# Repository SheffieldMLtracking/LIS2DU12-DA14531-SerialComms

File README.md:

# LIS2DU12-DA14531-SerialComms
Repo to develop LIS2DU12 communications with DA14531 BLE enabled microcontroller.

I've used the blinky example here to build the i2c stuff!

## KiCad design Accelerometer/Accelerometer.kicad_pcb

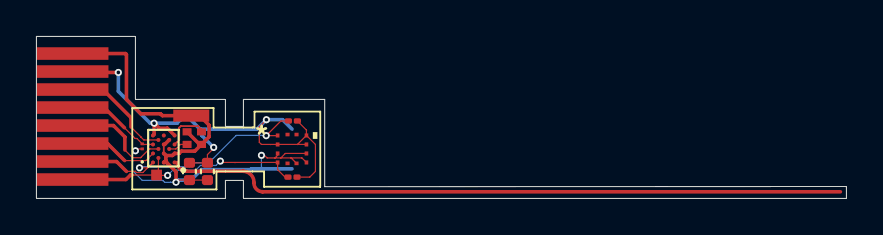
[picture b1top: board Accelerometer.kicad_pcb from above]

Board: 2 copper layers, 45.0 x 9.0 mm, 6 parts (0 on the bottom side), 10 nets.

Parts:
C1, C1#2: C; C_0402_1005Metric
J1: Conn_01x08_Pin; FPC_1x08_P1.00mm_plug_3mm
LED1: LED1; KPG-0402SURKKC-TT
U1: DA14531_17-ball_WLCSP
Y1: Crystal_GND24; Crystal_SMD_Abracon_ABM13W-4Pin_1.2x1.0mm

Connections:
/+VE: C1.1, C1#2.2, J1.7, U1.G1 (VBAT_LOW), U1.G5 (VBAT_HIGH)
/GND: C1.2, C1#2.1, J1.8, LED1.1, U1.A3 (RFIOm), U1.C1 (GND_RF2), U1.C3 (GND_RF1), U1.E3 (VSS), U1.F2 (GND_DCDC), Y1.2, Y1.4
unnamed: J1.1, U1.B4 (P0_3/XTAL32kp)
unnamed: J1.2, U1.A5 (P0_4/XTAL32km)
unnamed: J1.3, U1.C5 (P0_2/ADC1/SWCLK)
unnamed: J1.4, U1.D4 (P0_5/SWDIO)
unnamed: J1.5, LED1.2, U1.E5 (P0_1/ADC0/SWDIO)
unnamed: J1.6, U1.F4 (P0_0/RST)
unnamed: U1.E1 (XTAL32Mm), Y1.3
unnamed: U1.D2 (XTAL32Mp), Y1.1

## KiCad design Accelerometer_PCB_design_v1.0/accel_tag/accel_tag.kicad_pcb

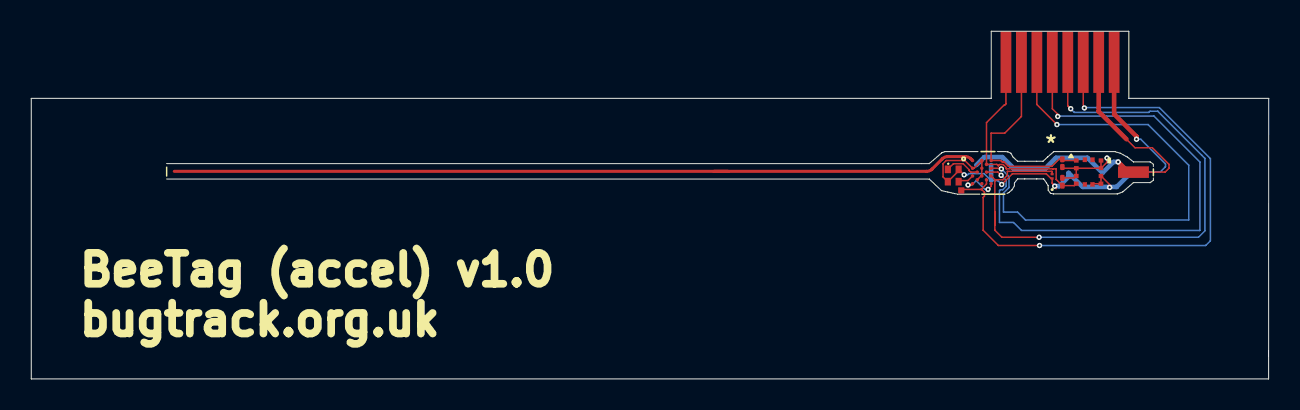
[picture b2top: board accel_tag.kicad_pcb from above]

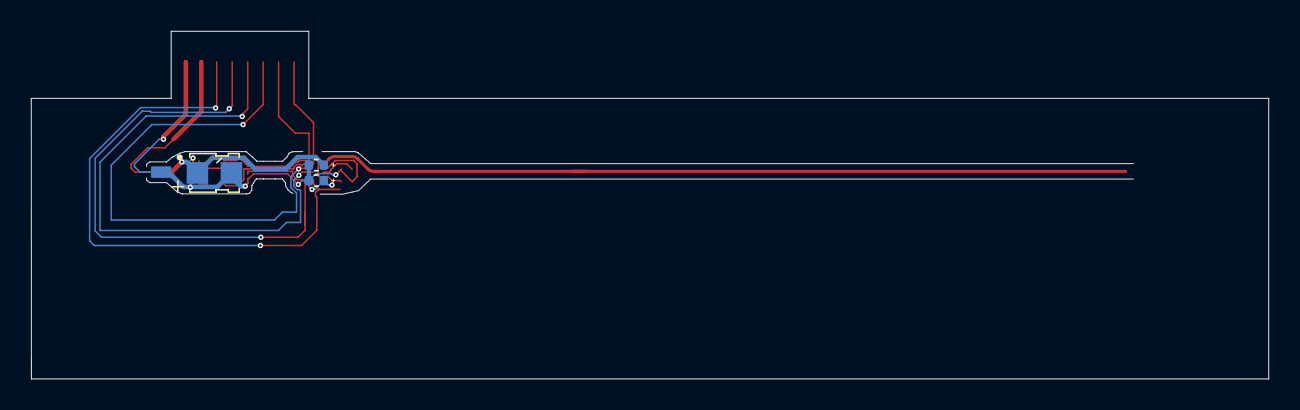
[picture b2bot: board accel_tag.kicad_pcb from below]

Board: 2 copper layers, 80.1 x 22.5 mm, 14 parts (4 on the bottom side), 10 nets.

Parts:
AE1: Antenna
C1: CPH3225A; CAPCP3225X100N_improved
C2, C3: C_Polarized; C_0402_1005Metric
CHARGING_GND1: Charging ground pin; Charging_pad_0.75x2mm
CHARGING_POSITIVE1: Charging positive pin; Charging_pad_0.75x2mm
D1: LED; KPG-0402SURKKC-TT
J1: Conn_01x08; FPC_1x08_P1.00mm_plug_3mm
R1, R2: 10K; R_01005_0402Metric
TP1: TestPoint; TestPoint_Pad_1.0x1.0mm
U1: LIS2DU12TR; LGA-12L_LIS2DU12_STM
U2: DA14531-00000OG2; DA14531_17-ball_WLCSP
Y1: ABM13W-32MHz; Crystal_SMD_Abracon_ABM13W-4Pin_1.2x1.0mm

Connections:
GNDREF: C1.2, C2.2, C3.2, CHARGING_GND1.1, D1.1 (K), J1.8, U1.6 (GND), U1.7 (RES), U1.8 (GND), U2.A3 (RFIOM), U2.C1 (GND_RF2), U2.C3 (GND_RF1), U2.E3 (VSS), U2.F2 (GND_DCDC), Y1.2 (GND), Y1.4 (NC)
unnamed: D1.2 (A), J1.5, U2.E5 (P0_1/ADC0/SWDIO)
unnamed: J1.1, R2.2, U1.4 (SDA/SDI/SDO), U2.B4 (P0_3/XTAL32KP)
unnamed: J1.2, R1.2, U1.1 (SCL/SPC), U2.A5 (P0_4/XTAL32KM)
unnamed: J1.3, U2.C5 (P0_2/ADC1/SWCLK)
unnamed: J1.4, U2.D4 (P0_5/SWDIO)
unnamed: J1.6, TP1.1, U2.F4 (RST/P0_0)
unnamed: C1.1, C2.1, C3.1, CHARGING_POSITIVE1.1, J1.7, R1.1, R2.1, U1.2 (CS), U1.3 (SDO/SA0), U1.9 (VDD), U1.10 (VDD_IO), U2.G1 (VBAT_LOW), U2.G5 (VBAT_HIGH)
unnamed: U2.E1 (XTAL32MM), Y1.3
unnamed: U2.D2 (XTAL32MP), Y1.1

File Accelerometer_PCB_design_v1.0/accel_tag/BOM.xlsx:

|  |  | xxxx xxxx xxxxx xxPCS BOM (Sample Bill of Materials)
Item # | *Designator | *Qty | Manufacturer | *Mfg Part # | Description / Value | *Package/Footprint | Type | Your Instructions / Notes
1 | C2 | 1 | KYOCERA AVX | CM05X5R226M04AH | Multilayer Ceramic Capacitors SMD, 22 µF, 4V. [note if different cap is used: n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 | 0402 [1005 Metric] | SMD | Positive pin indicated with silkscreen +.
2 | C3 | 1 | KYOCERA AVX | CM05X5R226M04AH | Multilayer Ceramic Capacitors SMD, 22 µF, 4V. [note if different cap is used: n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 | 0402 [1005 Metric] | SMD | Positive pin indicated with silkscreen +.
3 | U2 | 1 | Renesas / Dialog | DA14531-00000OG2 | Bluetooth Low Energy 5.1 SoC with integrated ARM Cortex M0+ | WLCSP-17 | SMD | Pin A1 indicated with silkscreen circle (at top left, close to part Y1)
3 | Y1 | 1 | Seiko Semiconductors | ABM13W-32.0000MHZ-5-DH7G-T5 | 32.0000MHz Quartz Crystal. 5pF load cap. 7ppm freq tol. 15ppm freq stab. [requi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 | SMD (4 pins) | SMD | Pin 1 indicated by silkscreen dot (nearest IC). Note that it is pin 2 that has 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
4 | C1 | 1 | Seiko Semiconductors | CPH3225A | Supercapacitor: electric double layer capacitor. 3.3V, 11mF, (internal impedanc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 | SMD (2 pins), 3.2mm x 2.5mm | SMD | Positive pin indicated wit silkscreen h + and dot. Also shape of capacitor has 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
5 | D1 | 1 | Kingbright | KPG-0402SURKKC-TT | 0.45 mm x 0.25 mm SMD Hyper red LED, 0.2 mm thickness. AlGaInP on GaAs substrat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 | 0402 [1005 Metric] | SMD | LED is placed in reverse bias, pin 1 goes to GND and pin 2 goes to a pin of par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
6 | U1 | 1 | STMicroelectronics | LIS2DU12TR | 2 mm x 2 mm x 0.74 mm Ultralow-power accelerometer with antialiasing and motion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 | LGA-12L | SMD | Pin 1 indicated by silkscreen triangle (close to part R1). Pin 1 is notched on 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
7 | R1 | 1 | Bourns | CR0402-JW-103GLF | 1 mm x 0.5mm SMD 10k Ohm Thick Film Resistor, 0.32 mm thickness. 5% tolerance. 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 | 0402 [1005 Metric] | SMD
8 | R2 | 1 | Bourns | CR0402-JW-103GLF | 1 mm x 0.5mm SMD 10k Ohm Thick Film Resistor, 0.32 mm thickness. 5% tolerance. 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 | 0402 [1005 Metric] | SMD
Need a quick and accurante quote? Need an efficient production? Please read SMT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
Click for Instructions on How to Create a BOM

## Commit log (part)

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2025-12-12 Added accelerometer PCB project folder
2025-12-12 Connected BLE tag with accelerometer aswell as checking design rules. Still not complete yet
2025-12-18 updated PCB with correct pin connections
2025-12-19 Double checked schematic
2026-01-22 An attempt to make the accel. version of the tag
2026-01-22 Make a little narrower
2026-01-22 Make even more narrow.
2026-01-27 tweaking tracks around crystal; narrower perimeter
2026-01-28 Added BOM, silkscreen instructions
2026-01-29 Fifo reading when full and dumps in to varible
2026-02-11 Added FFT implementation using CMSIS python wrapper
2026-02-19 Added DWT asswell as detrending data before hand
